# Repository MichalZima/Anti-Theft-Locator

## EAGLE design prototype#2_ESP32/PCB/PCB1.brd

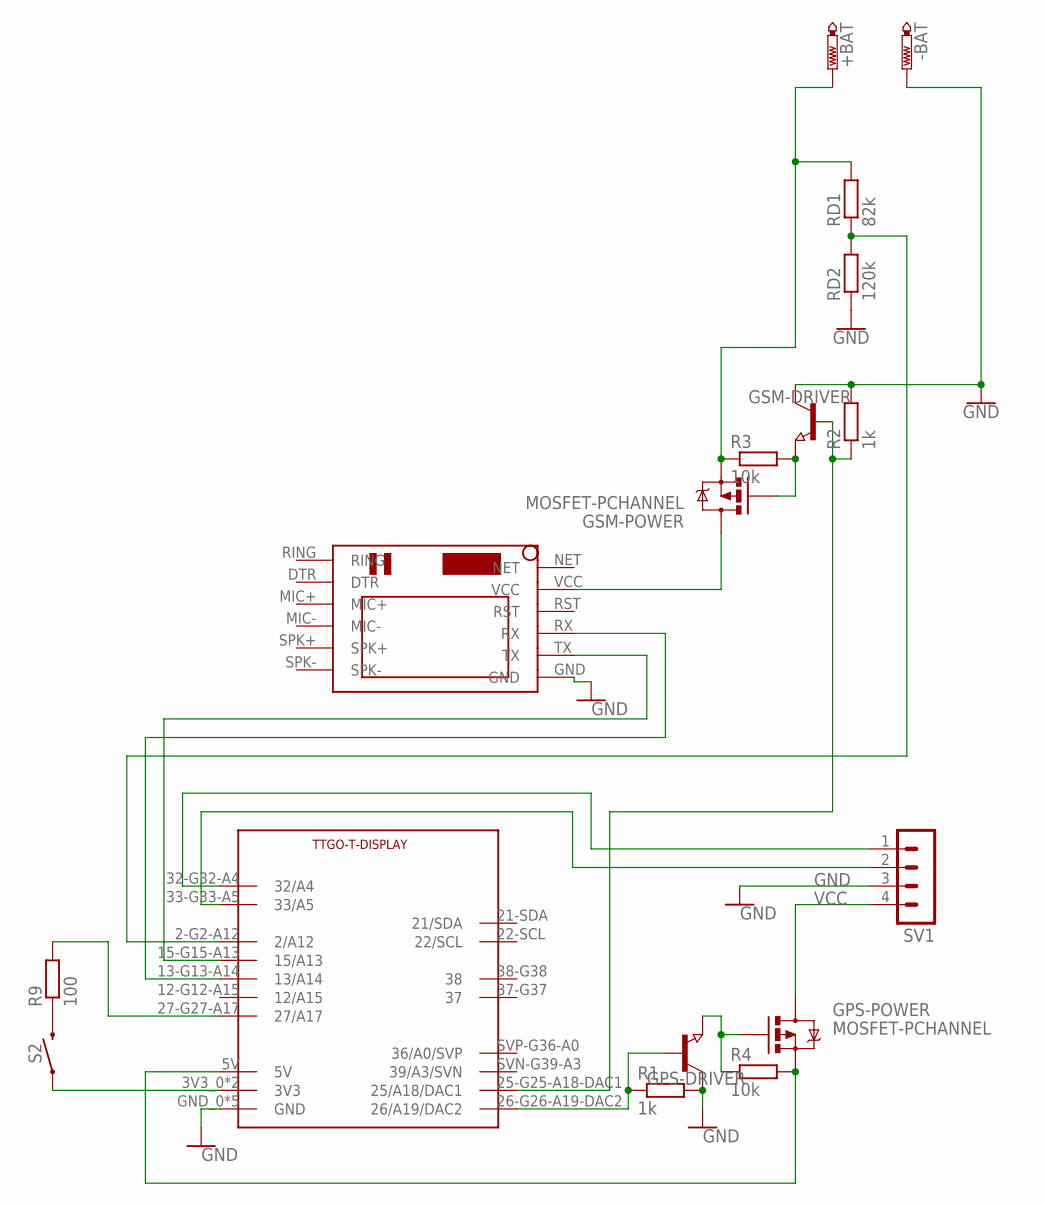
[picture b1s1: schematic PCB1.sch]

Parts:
+BAT: PTR1PAD1-13Y; P1-13Y
-BAT: PTR1PAD1-13Y; P1-13Y
GPS-DRIVER: NPN-TRANSISTOR_SOT23; SOT23
GPS-POWER: MOSFET-PCHANNEL; SOT23-3
GSM-DRIVER: NPN-TRANSISTOR_SOT23; SOT23
GSM-POWER: MOSFET-PCHANNEL; SOT23-3
R1, R2: 1k; R0402
R3, R4: 10k; R0603
R9: 100; R0603
RD1: 82k; R0402
RD2: 120k; R0402
S2: MOMENTARY-SWITCH-SPST-SMD-6.0X3.5MM; TACTILE_SWITCH_SMD_6.0X3.5MM
SV1: MA04-1
U$1: SIM800LMODULE
U$2: TTGO-T-DISPLAYFRAME; TTGO-T-DISPLAY-OL

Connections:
4/GSM_EN: GSM-DRIVER.1 (B), R2.1, U$2.25-G25-A18-DAC1 (25/A18/DAC1)
5/SCL: GPS-DRIVER.1 (B), R1.1, U$2.26-G26-A19-DAC2 (26/A19/DAC2)
5V: GPS-POWER.2 (S), R4.2, U$2.5V
17/TX2: U$1.RX, U$2.13-G13-A14 (13/A14)
18/TX1: SV1.2, U$2.33-G33-A5 (33/A5)
A0: RD1.1, RD2.2, U$2.2-G2-A12 (2/A12)
GND: -BAT.TP, GPS-DRIVER.3 (C), GSM-DRIVER.3 (C), R1.2, R2.2, RD2.1, SV1.3, U$1.GND, U$2.GND_0 (GND), U$2.GND_1 (GND), U$2.GND_2 (GND), U$2.GND_3 (GND), U$2.GND_4 (GND)
unnamed: R9.1, S2.2
unnamed: GPS-DRIVER.2 (E), GPS-POWER.1 (G), R4.1
unnamed: +BAT.TP, GSM-POWER.2 (S), R3.1, RD1.2
unnamed: GSM-POWER.3 (D), U$1.VCC
unnamed: GSM-DRIVER.2 (E), GSM-POWER.1 (G), R3.2
unnamed: SV1.1, U$2.32-G32-A4 (32/A4)
unnamed: U$1.TX, U$2.15-G15-A13 (15/A13)
unnamed: S2.1, U$2.3V3_0 (3V3), U$2.3V3_1 (3V3)
unnamed: R9.2, U$2.27-G27-A17 (27/A17)
VCC: GPS-POWER.3 (D), SV1.4

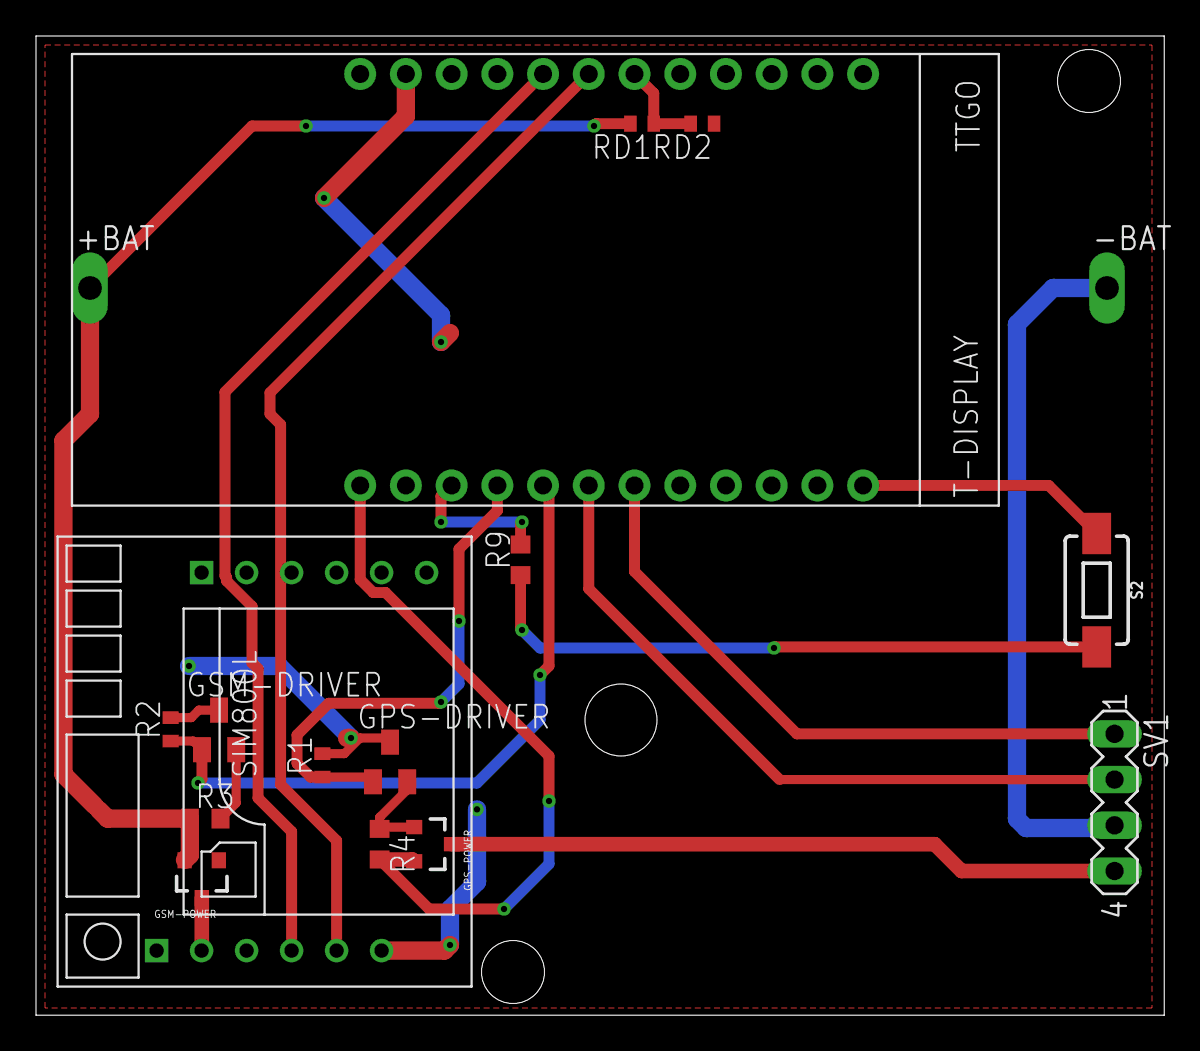
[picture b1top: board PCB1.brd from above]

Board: 2 copper layers, 62.7 x 54.4 mm, 17 parts (0 on the bottom side), 17 nets.

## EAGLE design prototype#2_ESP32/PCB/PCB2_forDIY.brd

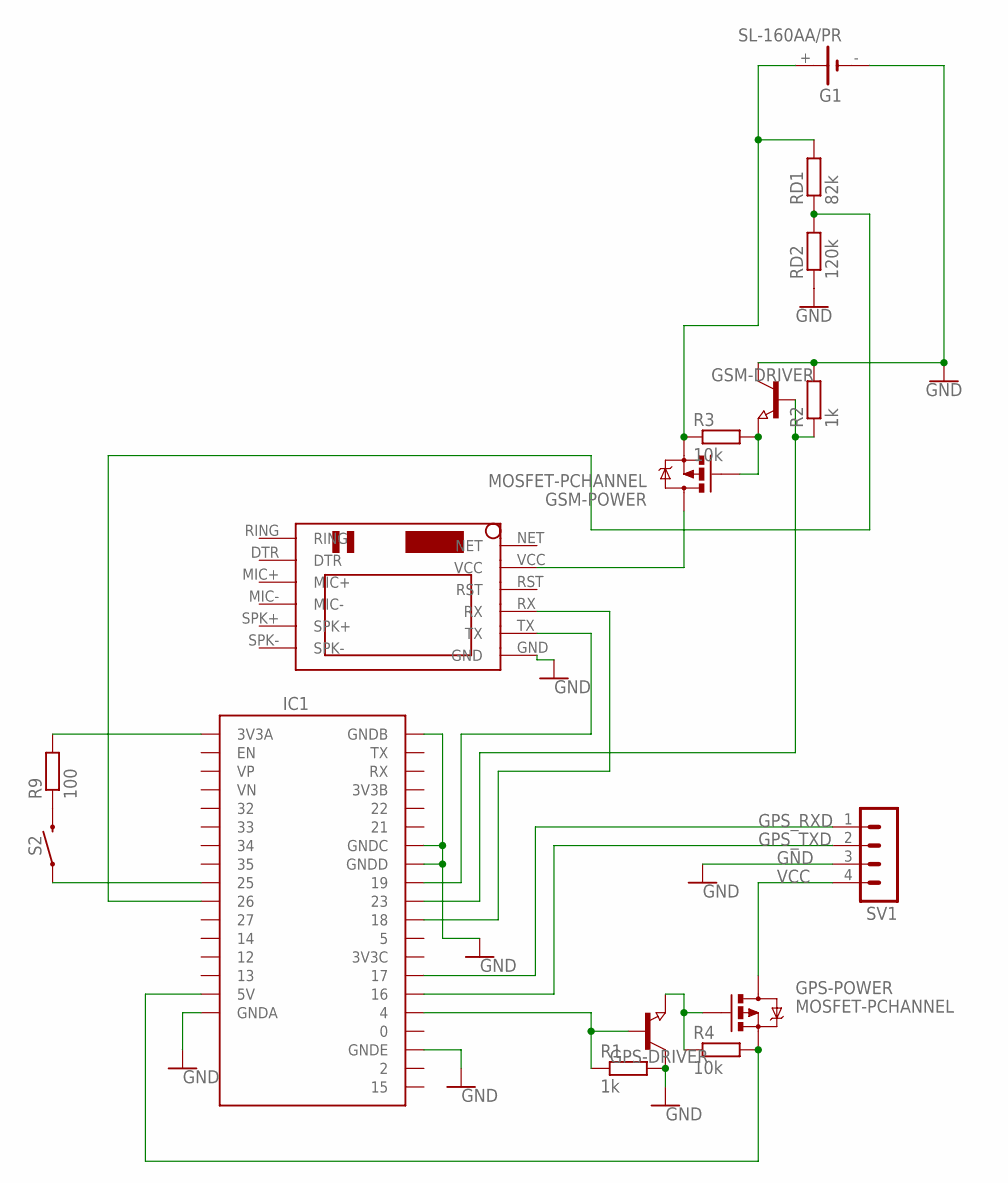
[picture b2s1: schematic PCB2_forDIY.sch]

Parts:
G1: SL-160AA/PR
GPS-DRIVER: NPN-TRANSISTOR_SOT23; SOT23
GPS-POWER: MOSFET-PCHANNEL; SOT23-3
GSM-DRIVER: NPN-TRANSISTOR_SOT23; SOT23
GSM-POWER: MOSFET-PCHANNEL; SOT23-3
IC1: SSFD_LOLIN32_WEMOS_CHINA_W_BATT
R1, R2: 1k; R0402
R3, R4: 10k; R0603
R9: 100; R0603
RD1: 82k; R0402
RD2: 120k; R0402
S2: MOMENTARY-SWITCH-SPST-SMD-6.0X3.5MM; TACTILE_SWITCH_SMD_6.0X3.5MM
SV1: MA04-1
U$1: SIM800LMODULE

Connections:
5/SCL: GPS-DRIVER.1 (B), IC1.4, R1.1
5V: GPS-POWER.2 (S), IC1.5V, R4.2
A0: IC1.26, RD1.1, RD2.2
CS/TXD2: GSM-DRIVER.1 (B), IC1.23, R2.1
GND: G1.-, GPS-DRIVER.3 (C), GSM-DRIVER.3 (C), IC1.GNDA, IC1.GNDB, IC1.GNDC, IC1.GNDD, IC1.GNDE, R1.2, R2.2, RD2.1, SV1.3, U$1.GND
GPS_RXD: IC1.17, SV1.1
GPS_TXD: IC1.16, SV1.2
unnamed: R9.1, S2.2
unnamed: GPS-DRIVER.2 (E), GPS-POWER.1 (G), R4.1
unnamed: G1.+, GSM-POWER.2 (S), R3.1, RD1.2
unnamed: GSM-POWER.3 (D), U$1.VCC
unnamed: GSM-DRIVER.2 (E), GSM-POWER.1 (G), R3.2
unnamed: IC1.18, U$1.RX
unnamed: IC1.19, U$1.TX
unnamed: IC1.3V3A, R9.2
unnamed: IC1.25, S2.1
VCC: GPS-POWER.3 (D), SV1.4

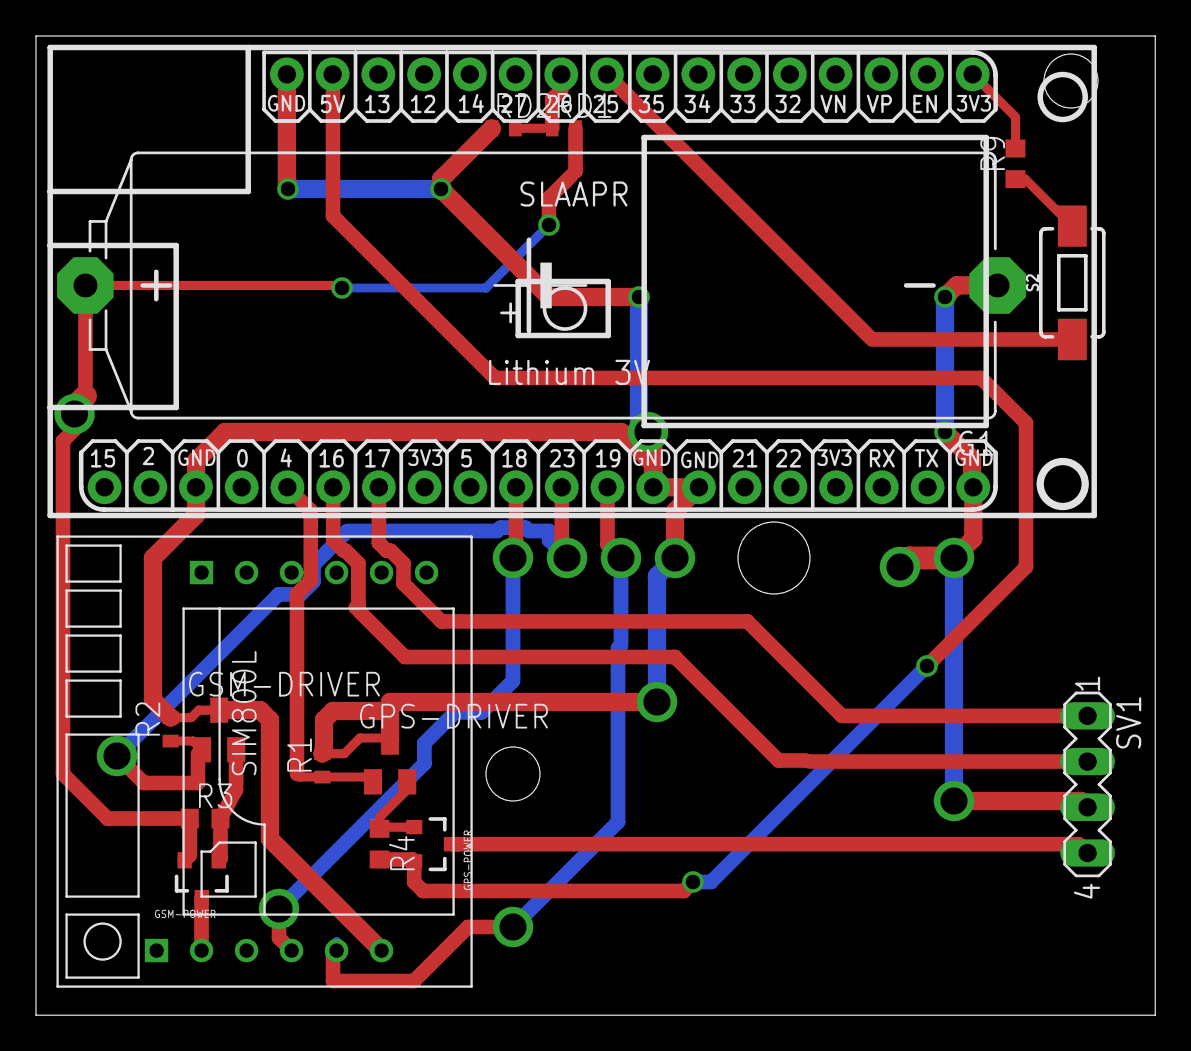
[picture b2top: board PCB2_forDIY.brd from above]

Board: 2 copper layers, 62.2 x 54.4 mm, 16 parts (0 on the bottom side), 17 nets.

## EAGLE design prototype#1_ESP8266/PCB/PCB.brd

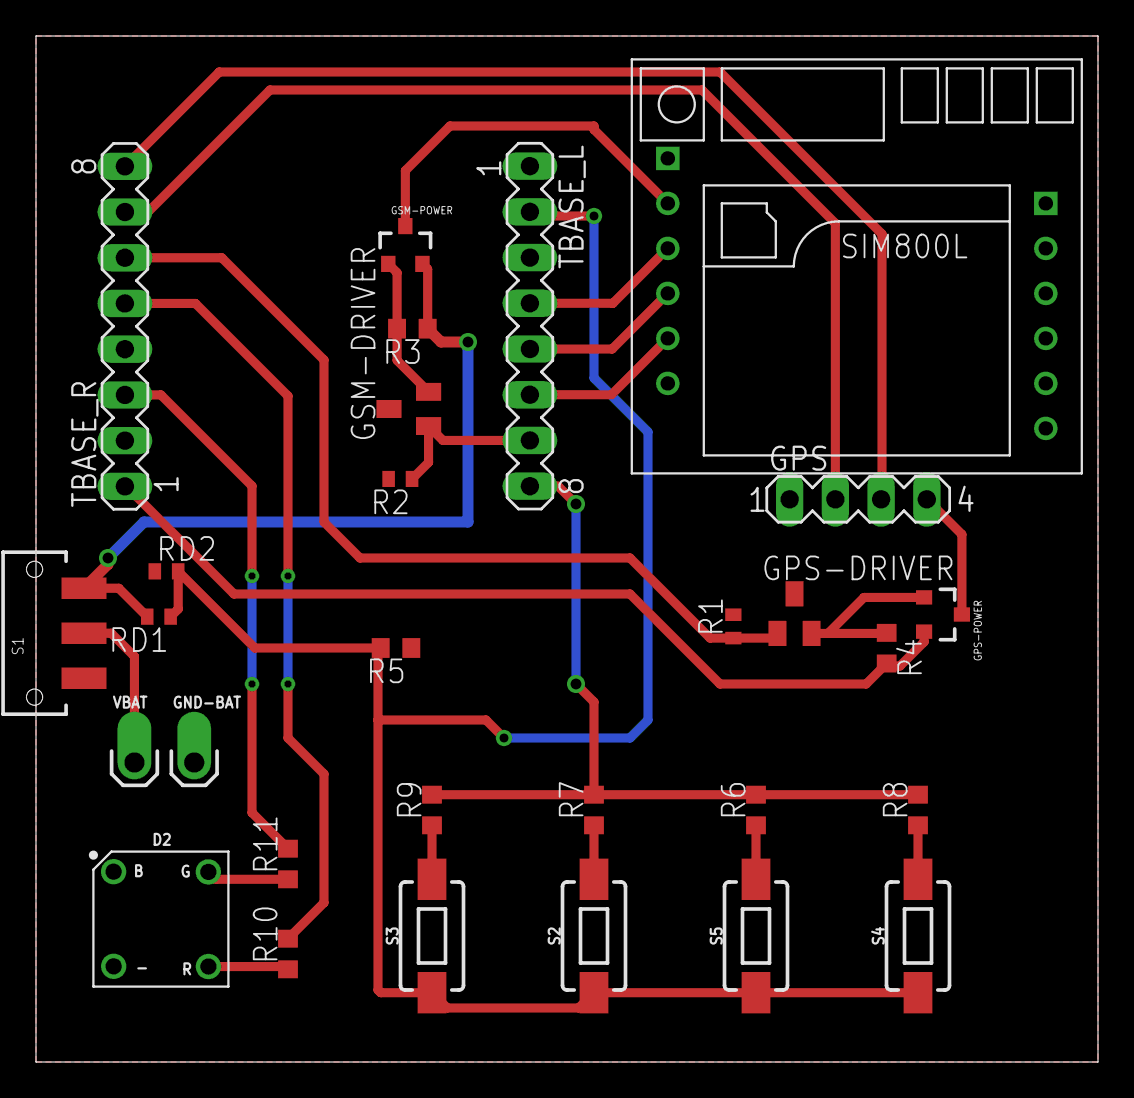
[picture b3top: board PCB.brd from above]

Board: 2 copper layers, 59.0 x 57.0 mm, 29 parts (0 on the bottom side), 26 nets.

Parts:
D2: LED_PIRANHA_5MM
GND-BAT: 1X01_OFFSET
GPS: MA04-1
GPS-DRIVER: SOT23
GPS-POWER: MOSFET-PCHANNEL; SOT23-3
GSM-DRIVER: SOT23
GSM-POWER: MOSFET-PCHANNEL; SOT23-3
R1, R2: 1k; R0402
R3, R4: 10k; R0603
R5: 1k; R0603
R6: 330; R0603
R7: 220; R0603
R8: 470; R0603
R9, R10, R11: 100; R0603
RD1: 82k; R0402
RD2: 120k; R0402
S1: SWITCH_SPDT_SMD
S2, S3, S4, S5: MOMENTARY-SWITCH-SPST-SMD-6.0X3.5MM; TACTILE_SWITCH_SMD_6.0X3.5MM
TBASE_L: MA08-1
TBASE_R: MA08-1
U$1: SIM800LMODULE
VBAT: 1X01_OFFSET

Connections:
2/TXD1: R11.2, TBASE_R.3
3.3V: R6.2, R7.2, R8.2, R9.2, TBASE_L.8
4/SDA: R10.2, TBASE_R.5
5/SCL: GPS-DRIVER.1, R1.1, TBASE_R.6
5V: GPS-POWER.2, R4.2, TBASE_R.1
A0: R5.2, RD1.1, RD2.2, S2.1, S3.1, S4.1, S5.1, TBASE_L.2
CS/TXD2: GSM-DRIVER.1, R2.1, TBASE_L.7
GND: D2.-, GND-BAT.1, GPS.1, GPS-DRIVER.3, GSM-DRIVER.3, R1.2, R2.2, R5.1, RD2.1, TBASE_R.2, U$1.GND
GPS-VCC: GPS.4, GPS-POWER.3
MISO: TBASE_L.5, U$1.RX
MOSI/RXD2: TBASE_L.6, U$1.TX
unnamed: S1.2, VBAT.1
unnamed: GPS-DRIVER.2, GPS-POWER.1, R4.1
unnamed: GSM-POWER.2, R3.1, RD1.2, S1.3
unnamed: GSM-POWER.3, U$1.VCC
unnamed: GSM-DRIVER.2, GSM-POWER.1, R3.2
unnamed: R8.1, S4.2
unnamed: R6.1, S5.2
unnamed: R7.1, S2.2
unnamed: R9.1, S3.2
unnamed: D2.R, R10.1
unnamed: D2.G, R11.1
RST: TBASE_L.1, TBASE_L.3
RXD: GPS.2, TBASE_R.7
SCLK: TBASE_L.4, U$1.RST
TXD: GPS.3, TBASE_R.8

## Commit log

2021-06-28 PCB for device
2021-06-28 placed components
2021-07-01 made test code
2021-07-03 added gps object
2021-07-03 edit code
2021-07-03 modified code
2021-07-03 working code
2021-07-05 finished scheme
2021-07-05 started pcb
2021-07-28 finished PCB
2022-03-06 edit test sketch
2022-03-06 main code
2022-03-06 case for device
2022-03-06 added rest
2022-03-06 deleted unnecessary files
2022-03-07 repaired unable printing
2022-03-07 added pin unlock functionality
2022-03-08 sketch for testing leds
2022-03-08 removed serial prints
2022-03-10 removed prints
2022-03-10 made blinking non interrupt]
2022-03-10 put everything together
2022-03-10 first working sketch
2022-03-10 finished prototype
2022-03-14 changed file name
2022-03-14 started esp32 version
2022-03-14 made platformio project
2022-03-14 moved esp8266 version files to folder prototype_#1_esp8266
2022-03-15 removed unneccesary files
2022-03-15 removed bad folder
2022-03-16 added debug print
2022-03-16 ESP32-GSM Version done and working
2022-03-16 debugged sending position
2022-03-16 change
2022-03-17 made pcb for esp32 version
2022-04-03 database
2022-04-03 finished pcb for prototype 2
2022-04-03 modified gitignore

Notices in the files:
parts and their libraries:
SparkFun-Connectors: Licensing: Creative Commons ShareAlike 4.0 International - https://creativecommons.org/licenses/by-sa/4.0
